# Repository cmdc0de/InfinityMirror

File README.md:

# InfinityMirror

## Materials you'll need:
* [Acrylic Mirror](https://www.amazon.com/Acrylic-Mirror-Sheet-Laser-Creations/dp/B01MXE417D/ref=sr_1_17?crid=3CSNSR02CE1KK&dchild=1&keywords=acrylic%2Bmirror%2Bsheet&qid=1609135905&s=home-garden&sprefix=acrylic%2Bmirror%2Cgarden%2C228&sr=1-17&th=1)
* [Acrylic see through Mirror](https://www.amazon.com/0-04-Acrylic-See-Through-Mirror-Transparent/dp/B07XTRC7F1?th=1)
* [ABS](https://www.raise3d.com/filaments/abs/) - I have a Raise 3D printer
* [22 Gauge Wire](https://www.amazon.com/gp/product/B00B4ZRPEY/ref=ppx_yo_dt_b_asin_title_o05_s02?ie=UTF8&psc=1)
* Solder 
* [Solder paste](https://www.amazon.com/Solder-Bi57-6-No-Clean-Lead-Free-Temperature/dp/B0195V1QEI/) - LOW TEMP solder
* Hot Glue
* [rechargable battery](https://www.amazon.com/Capacity-Rechargeable-Batteries-Flashlights-Headlamps/dp/B08MQDFQD4/)

## Equipment you'll need:
* 3d Printer
* laser cutter
* Solder Iron
* Hot Glue Gun

## Instructions
1. Mill/Etch/Order 20x Single-APA102c-breakout boards
2. Mill/Etch/Order 1x STM32G031J6M6 board
3. 3D Print: 3dprint/Base.stl, 3dprint/Base-bottom.stl, 3dprint/lid.stl, and 3dprint/octagon.stl
4. laser cut: laser-cutter/octagon v13.dxf 
5. Add components to the STM32G031J6M6 board.
6. Add componetns to 20x Single-APA102c-breakout boards - if you use an IR Oven make sure you use low temp solder!!! APA102c HATE 250 degress C!
7. Cut wires to length and connect all 20 Single-APA102c-breakout boards
8. Hot Glue apa102c breakouts into wholes of octogan - use a wire length of 3-4 inches for the first apa102c so you can feed it through the hole in the octagon and through the hole in the base to connect it to the STM32G031J6M6 baord.
9. Place acrylic mirror into bottom (it should fit via friction but I used a bit of CA glue as well).
10. place see through (2-way) mirror in the lid, again should fit via friction but I used a bit of CA glue as well.
11. Snap the lid on the octagon
12. Connect wires to STM32G031J6M6
13. Program the STM32G031J6M6 via J-LInk or ST-LInk connector and [STM32CubeIDE](https://www.st.com/en/development-tools/stm32cubeide.html)
  1. Open project in firmware directory
  2. compile and program 
14. Hot Glue board to bottom-lid such that the STM32G031J6M6 board fits in the whole in the base.
15. Connect a rechargable 3.7-5V battery to the screw terminals 
16. Connect Base-bottom to base

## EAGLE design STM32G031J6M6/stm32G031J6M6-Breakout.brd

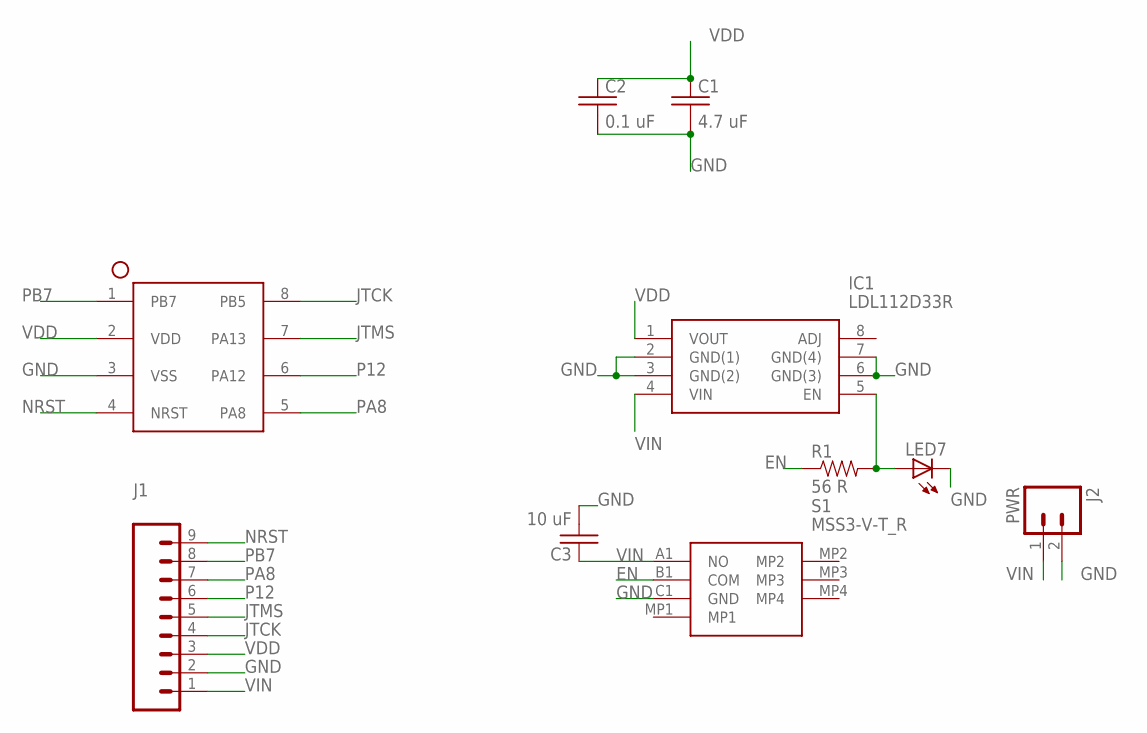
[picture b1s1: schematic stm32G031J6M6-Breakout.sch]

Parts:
C1: 4.7 uF; C0805K
C2: 0.1 uF; C0805K
C3: 10 uF; C0805K
IC1: LDL112D33R; SOIC127P600X175-8N
J1: M09LONGPADS; 1X09_LONGPADS
J2: PWR; SCREWTERMINAL-5MM-2
LED7: LED1206; LED-1206
R1: 56 R; 1206
S1: MSS3-V-T_R; MSS3VTR
U$1: STM32G031S08N; SOIC127P600X175-8N

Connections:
EN: R1.1, S1.B1 (COM)
GND: C1.2, C2.2, C3.2, IC1.2 (GND(1)), IC1.3 (GND(2)), IC1.6 (GND(3)), IC1.7 (GND(4)), J1.2, J2.2, LED7.C, S1.C1 (GND), U$1.3 (VSS)
JTCK: J1.4, U$1.8 (PB5)
JTMS: J1.5, U$1.7 (PA13)
unnamed: IC1.5 (EN), LED7.A, R1.2
NRST: J1.9, U$1.4 (NRST)
P12: J1.6, U$1.6 (PA12)
PA8: J1.7, U$1.5 (PA8)
PB7: J1.8, U$1.1 (PB7)
VDD: C1.1, C2.1, IC1.1 (VOUT), J1.3, U$1.2 (VDD)
VIN: C3.1, IC1.4 (VIN), J1.1, J2.1, S1.A1 (NO)

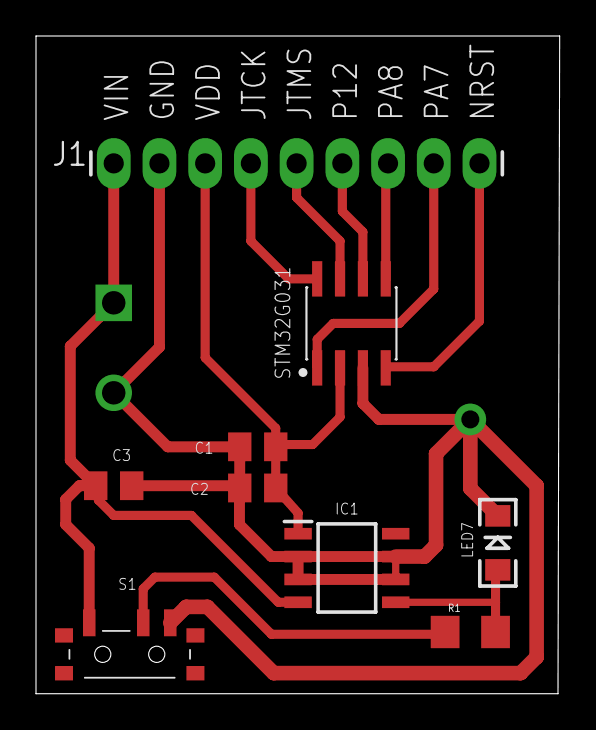
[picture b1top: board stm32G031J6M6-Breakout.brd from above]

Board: 2 copper layers, 29.1 x 36.5 mm, 10 parts (1 on the bottom side), 11 nets.

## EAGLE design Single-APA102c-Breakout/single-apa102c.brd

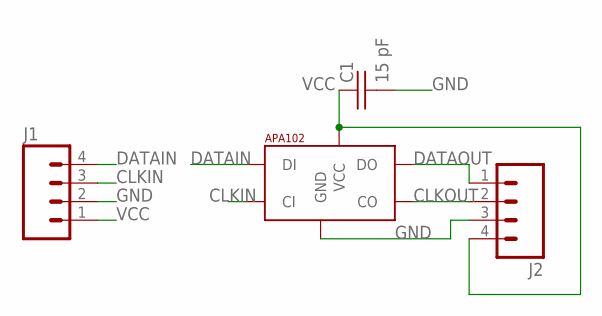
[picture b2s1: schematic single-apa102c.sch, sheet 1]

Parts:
C1: 15 pF; C0805K
J1, J2: M04PTH; 1X04
U$1: APA1025050; APA102_5050

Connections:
CLKIN: J1.3, U$1.5 (CI)
CLKOUT: J2.2, U$1.2 (CO)
DATAIN: J1.4, U$1.4 (DI)
DATAOUT: J2.1, U$1.3 (DO)
GND: C1.2, J1.2, J2.3, U$1.6 (GND)
VCC: C1.1, J1.1, J2.4, U$1.1 (VCC)

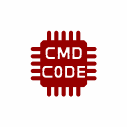
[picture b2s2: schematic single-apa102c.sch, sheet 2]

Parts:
U$2: CMD_C0DE_LOGOCMD_CODE_LOGO_SILK; CMD_C0DE_LOGO_SILK

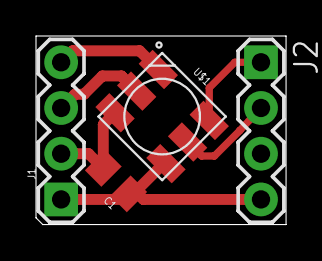
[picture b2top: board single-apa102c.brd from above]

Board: 2 copper layers, 13.9 x 10.5 mm, 5 parts (1 on the bottom side), 6 nets.

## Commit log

2020-11-21 initial checkin
2020-11-22 inital setup
2020-12-12 base code
2020-12-12 updated libstm32
2020-12-12 working
2020-12-12 adding 3d print files
2020-12-26 adding new code but not working
2020-12-27 working code with 5 different dances
2020-12-27 new libstm32
2020-12-27 fixed warning
2020-12-28 Update README.md
    initial instructions
